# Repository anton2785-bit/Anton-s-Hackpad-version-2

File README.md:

# Anton-s-Hackpad-versuon-2

---
## What is this project

* The mini hackpad's purpose is to make my life a little easier. It does it in the form of shortcuts. The display will be used to show information like the shortcut layer, that the hackpad is on ( For example instead of 12 buttons for shortcuts I have 24 or more ). The rotary encoder could be programmed to do anything. I am going to probably make it adjust my volume or cycle trough profiles/layers of shortcuts. 
---
## Why i made this project/hackpad

* I made this hackpad do make my life easier. It will do this by being programmed with shortcuts (or actions) that will save me 1 or 2 clicks on my mouse per action. For example I want to have a shortcut for some apps and sites to oppen at the same time in one configuration (the site on the left and the app on the right).
## Images

* PCB                         
* 
* Schematic 
* 
*  Assembly
* 

---

## Case & Mounting

* The case is **fully 3D‑printed** 
* PCB is placed directly to the case and it rests there 

---

## Assembly steps

1. Solder all components to the PCB.
2. Place the assembled PCB in the case (The PCB just rests there, no bolts throug it)
3. Bolt the top plate to the bottom one with heat inserts
4. Attach the switches with the keycaps in the hotswap modules.

* I will add photos to the process once i get the parts

---

## Firmware

* I used KMK for this project, but ill improve it when i get the hackpad
* Claude helprd a bit for this part: The screen interface for now is not human made, but once I get all the parts needed for testing it.

---

## Perfect for:

* Coding shortcuts
* CAD 
* Learning keyboard firmware

---

## Bill of Materials (BOM)

| Name | Purpose | Qty | Cost (USD) | Distributor |
|------|---------|-----|------------|-------------|
| [Hotswap modules](https://www.gateron.com/products/gateron-hot-swap-pcb-socket?VariantsId=10170) | Making the switches removable | 1 | $7.00 | Gateron |
| [Switches](https://www.gateron.com/products/gateron-smoothie-silver-switch-set?VariantsId=11394) | Buttons | 1 | $14.73 | Gateron |
| [Diodes](https://www.aliexpress.com/item/1005007160563285.html) | Make the signal go in one direction | 1 | $2.18 | AliExpress |
| [Rotary encoder](https://www.aliexpress.com/item/1005006111225091.html) | Probably for volume | 1 | $3.30 | AliExpress |
| PCB | The place for everything | 1 | $3.50 | JLCPCB |
| [XIAO RP2040](https://www.seeedstudio.com/XIAO-RP2040-v1-0-p-5026.html) | The brain for the thing | 1 | $13.70 | Seeed Studio |
| [128x32 screen](https://www.aliexpress.com/item/1005008640132638.html) | Showing some information | 1 | $2.27 | AliExpress |
| **Total** | | | **$46.68** | |
## Credits

Designed and built by *(Anton/ Anton-2785-bit)*
Inspired by open‑source mechanical keyboard and hackpad communities (https://stasis.hackclub.com/dashboard).

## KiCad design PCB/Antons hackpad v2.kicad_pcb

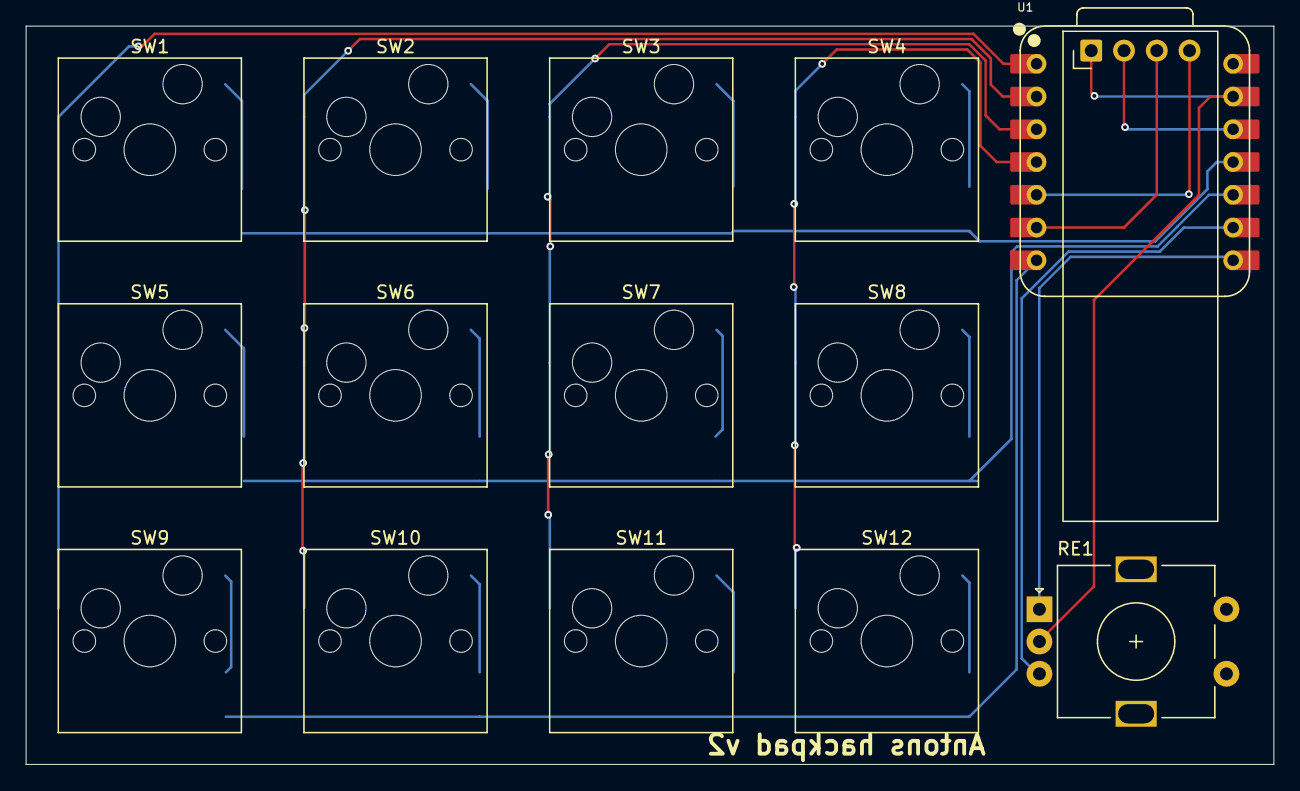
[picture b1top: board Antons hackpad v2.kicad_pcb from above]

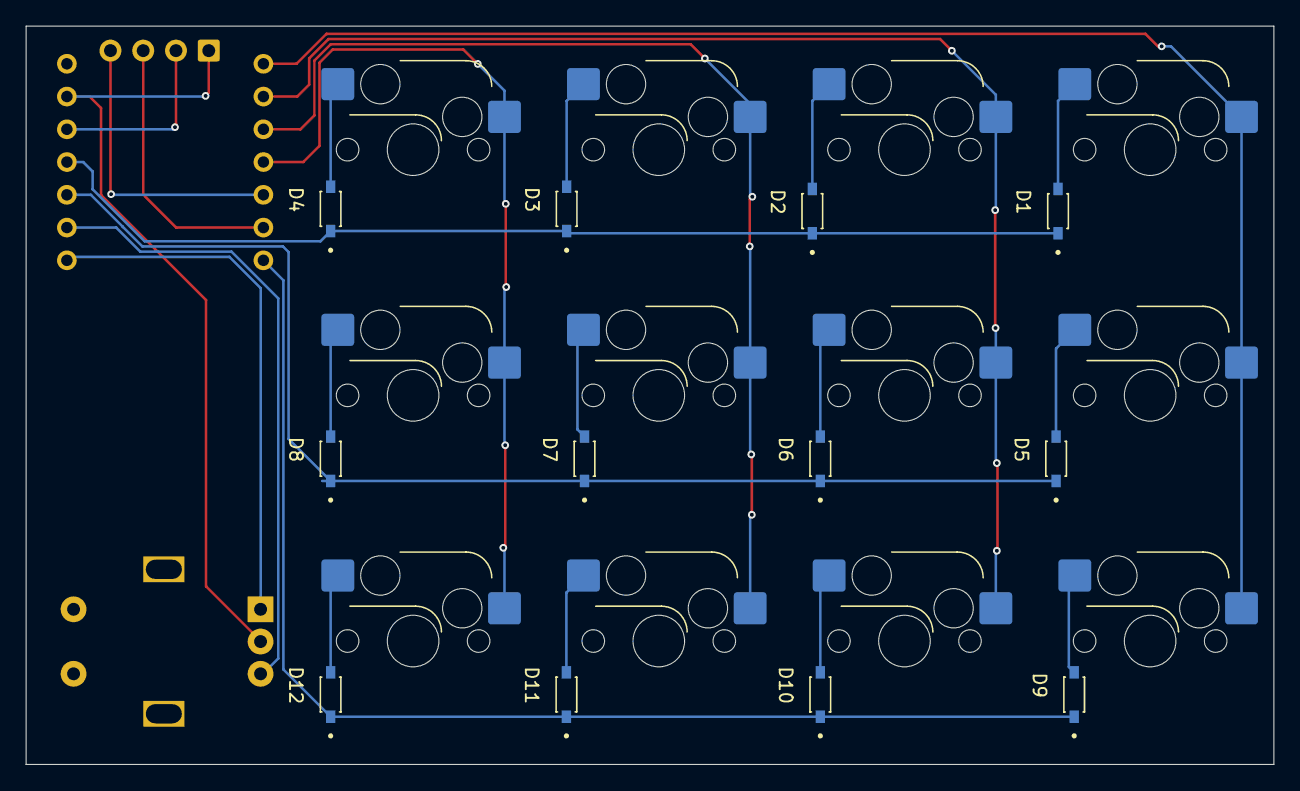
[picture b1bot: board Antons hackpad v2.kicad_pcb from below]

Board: 2 copper layers, 96.8 x 57.2 mm, 27 parts (12 on the bottom side), 25 nets.

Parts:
D1, D2, D3, D4, D5, D6, D7, D8, D9, D10, D11, D12: 1N4148W; SODFL3816X120N
RE1: RotaryEncoder_Switch_MP; RotaryEncoder_Alps_EC11E-Switch_Vertical_H20mm
SW1, SW2, SW3, SW4, SW5, SW6, SW7, SW8, SW9, SW10, SW11, SW12: SW_Push_45deg; Hotswap_MX_1.00u
U1: XIAO-RP2040-DIP
U2: OLED_0.91_128x32

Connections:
+3.3V: U1.12 (3V3), U2.2 (VCC)
GND: RE1.C, U1.13 (GND), U2.1 (GND)
unnamed: D1.A, SW1.2
unnamed: D2.A, SW2.2
unnamed: D3.A, SW3.2
unnamed: D4.A, SW4.2
unnamed: D5.A, SW5.2
unnamed: D6.A, SW6.2
unnamed: D7.A, SW7.2
unnamed: D8.A, SW8.2
unnamed: D9.A, SW9.2
unnamed: D10.A, SW10.2
unnamed: D11.A, SW11.2
unnamed: D12.A, SW12.2
Rotary A: RE1.A, U1.8 (GPIO1/RX)
Rotary B: RE1.B, U1.9 (GPIO2/SCK)
Screen 1: U1.5 (GPIO6/SDA), U2.4 (SDA)
Screen 2: U1.6 (GPIO7/SCL), U2.3 (SCL)
column 1: SW1.1, SW5.1, SW9.1, U1.1 (GPIO26/ADC0/A0)
column 2: SW2.1, SW6.1, SW10.1, U1.2 (GPIO27/ADC1/A1)
column 3: SW3.1, SW7.1, SW11.1, U1.3 (GPIO28/ADC2/A2)
column 4: SW4.1, SW8.1, SW12.1, U1.4 (GPIO29/ADC3/A3)
row 1: D1.C, D2.C, D3.C, D4.C, U1.11 (GPIO3/MOSI)
row 2: D5.C, D6.C, D7.C, D8.C, U1.10 (GPIO4/MISO)
row 3: D9.C, D10.C, D11.C, D12.C, U1.7 (GPIO0/TX)

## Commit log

2026-03-31 File update
2026-03-31 Update README formatting and section header
2026-03-31 Update firmware section in README
    Clarified contribution details and added image reference.
2026-03-31 Update files
